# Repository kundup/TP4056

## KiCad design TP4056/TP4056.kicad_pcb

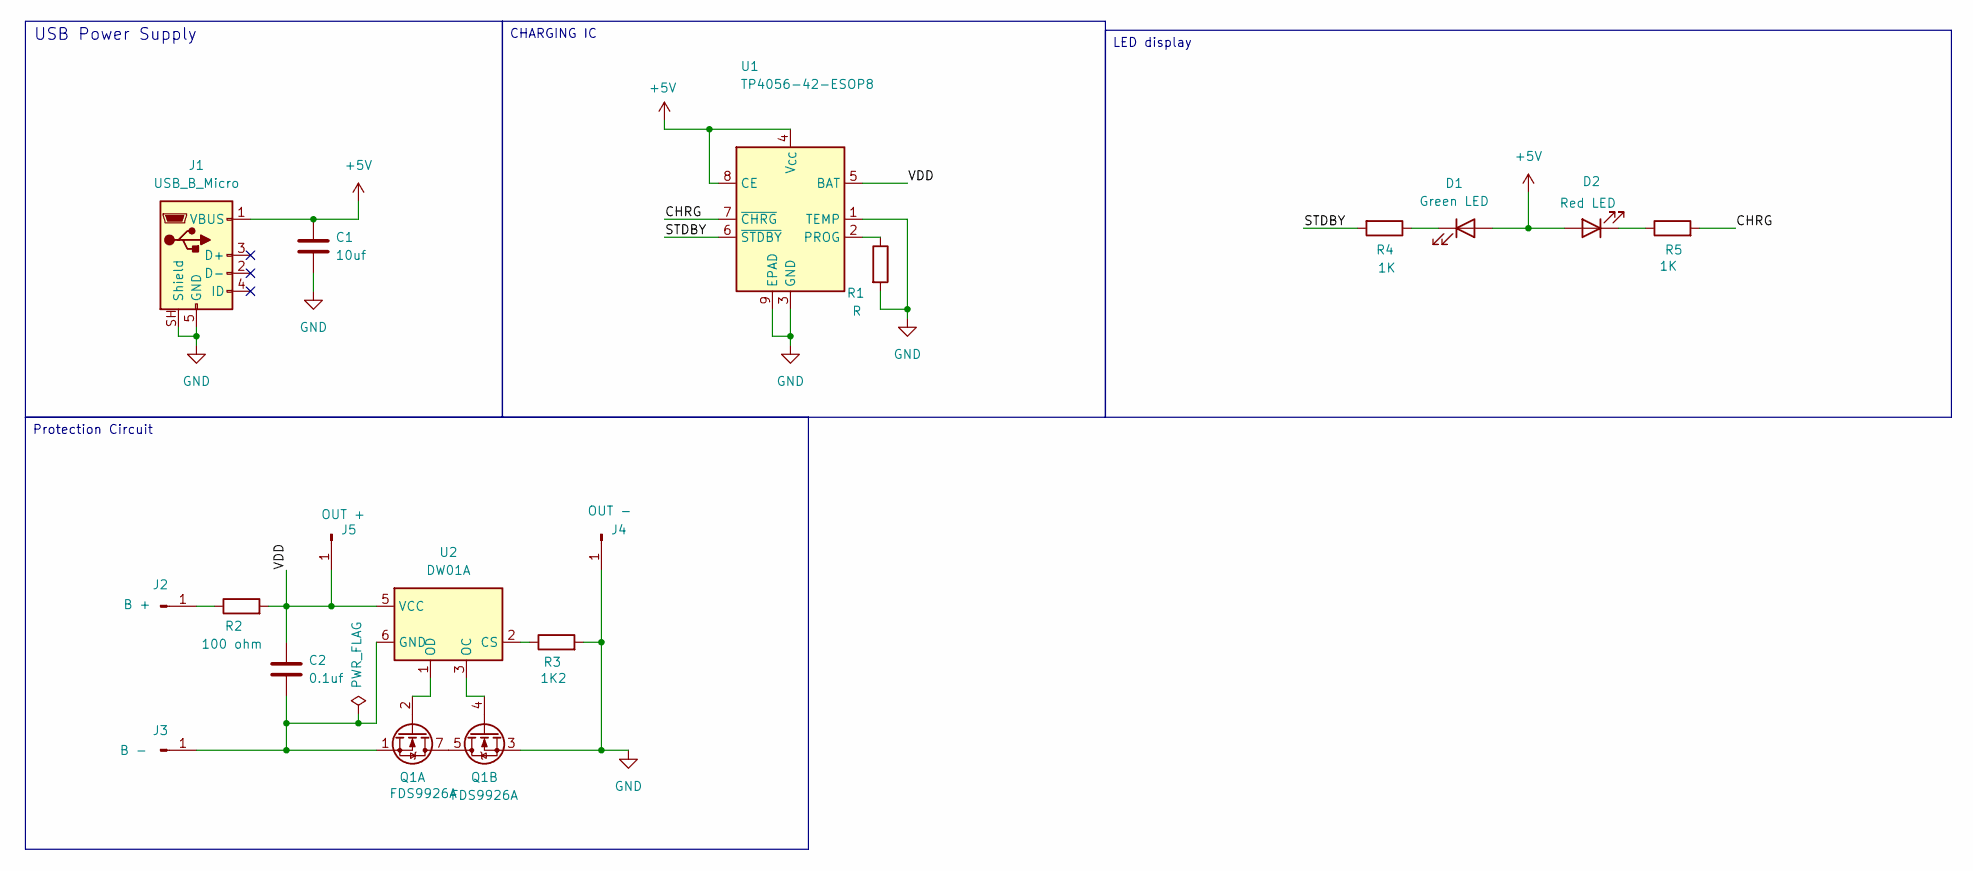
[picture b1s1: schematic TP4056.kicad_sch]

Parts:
C1: 10uf; C_0805_2012Metric
C2: 0.1uf; C_0805_2012Metric
D1: Green LED; LED_D1.8mm_W3.3mm_H2.4mm
D2: Red LED; LED_D1.8mm_W3.3mm_H2.4mm
J1: USB_B_Micro; USB_Micro-B_Amphenol_10118194-0001LF_Horizontal
J2: B +; SolderWirePad_1x01_SMD_1x2mm
J3: B -; SolderWirePad_1x01_SMD_1x2mm
J4: OUT -; SolderWirePad_1x01_SMD_3x6mm
J5: OUT +; SolderWirePad_1x01_SMD_3x6mm
Q1: FDS9926A; SOIC-8_3.9x4.9mm_P1.27mm
R1: R; R_Axial_DIN0204_L3.6mm_D1.6mm_P5.08mm_Horizontal
R2: 100 ohm; R_Axial_DIN0204_L3.6mm_D1.6mm_P5.08mm_Horizontal
R3: 1K2; R_Axial_DIN0204_L3.6mm_D1.6mm_P5.08mm_Horizontal
R4, R5: 1K; R_Axial_DIN0204_L3.6mm_D1.6mm_P5.08mm_Horizontal
U1: TP4056-42-ESOP8; SOIC-8-1EP_3.9x4.9mm_P1.27mm_EP2.41x3.3mm_ThermalVias
U2: DW01A; SOT-23-6

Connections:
+5V: C1.1, D1.2 (A), D2.2 (A), J1.1 (VBUS), U1.4 (V_{CC}), U1.8 (CE)
/CHRG: R5.2, U1.7 (~CHRG)
/STDBY: R4.2, U1.6 (~STDBY)
/VDD: C2.1, J5.1 (Pin_1_1), R2.2, U1.5 (BAT), U2.5 (VCC)
GND: C1.2, J1.5 (GND), J1.SH (Shield), J4.1 (Pin_1_1), Q1.3 (S2), R1.2, R3.2, U1.1 (TEMP), U1.3 (GND), U1.9 (EPAD)
unnamed: D1.1 (K), R4.1
unnamed: D2.1 (K), R5.1
unnamed: J2.1 (Pin_1_1), R2.1
unnamed: C2.2, J3.1 (Pin_1_1), Q1.1 (S1), U2.6 (GND)
unnamed: Q1.5 (D2), Q1.6 (D2), Q1.7 (D1), Q1.8 (D1)
unnamed: Q1.2 (G1), U2.1 (OD)
unnamed: Q1.4 (G2), U2.3 (OC)
unnamed: R1.1, U1.2 (PROG)
unnamed: R3.1, U2.2 (CS)

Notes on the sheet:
USB Power Supply
Protection Circuit
CHARGING IC
LED display

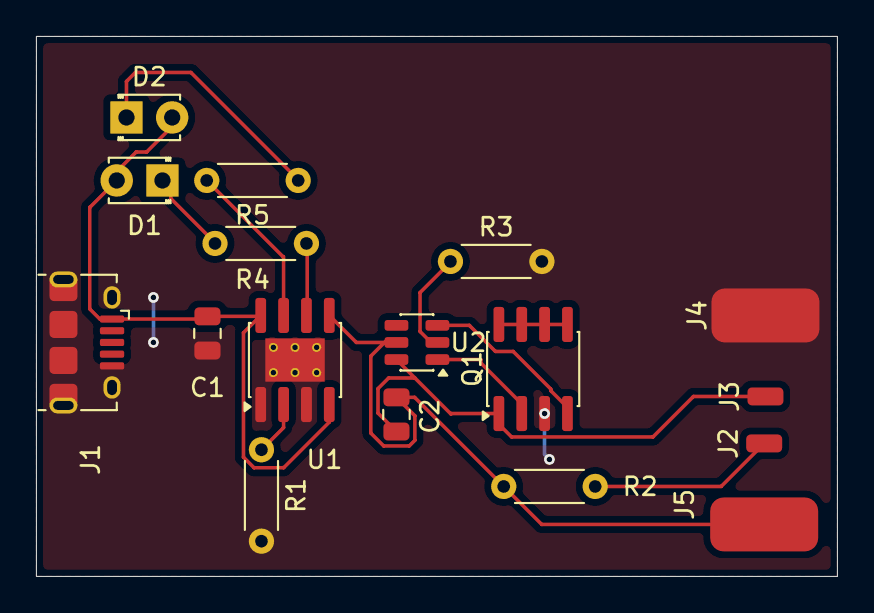
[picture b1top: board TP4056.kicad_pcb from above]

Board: 2 copper layers, 44.5 x 30.0 mm, 17 parts (0 on the bottom side), 14 nets.
